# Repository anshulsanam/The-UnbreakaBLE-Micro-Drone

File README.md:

# The-UnbreakaBLE-Micro-Drone

This repo contains all the hardware for the drone including schematics, board files, and even 3d print files.

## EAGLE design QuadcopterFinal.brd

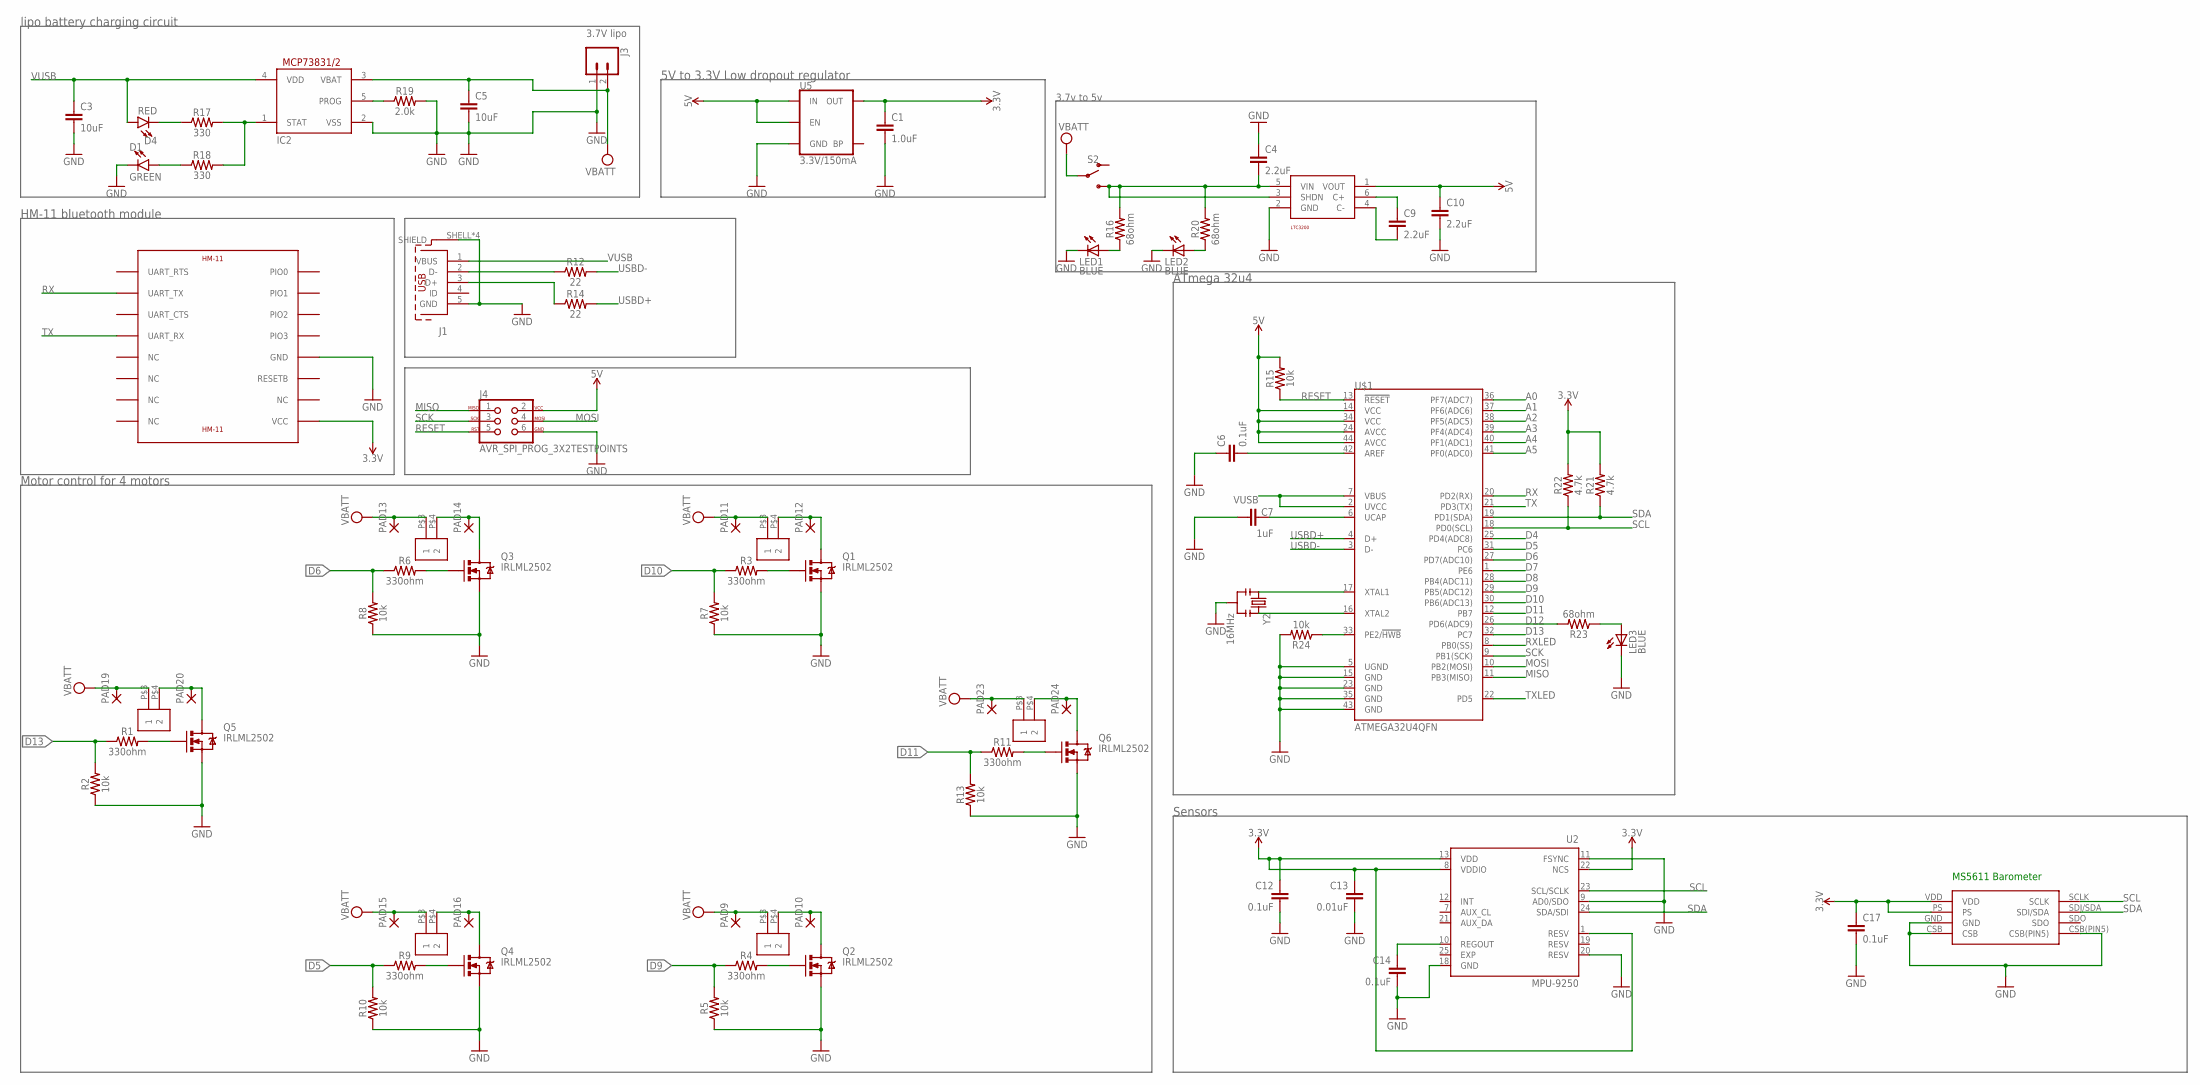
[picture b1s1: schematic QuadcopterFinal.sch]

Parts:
C1: 1.0uF; 0402
C3, C5: 10uF; 0603
C4, C9, C10: 2.2uF; 0603
C6, C12, C14, C17: 0.1uF; 0402
C7: 1uF; 0402
C13: 0.01uF; C0402
D1: GREEN; LED-0603
D4: RED; LED-0603
IC2: MCP73831/OT; SOT23-5L
J1: 629105136821
J3: CONN_021X02_NO_SILK; 1X02_NO_SILK
J4: AVR_SPI_PROG_3X2TESTPOINTS; 2X3_TEST_POINTS
LED1, LED2, LED3: BLUE; CHIPLED_1206
LTC3200: LTC3200
PAD9, PAD10, PAD11, PAD12, PAD13, PAD14, PAD15, PAD16, PAD19, PAD20, PAD23, PAD24: SMD2; SMD1,27-2,54
Q1, Q2, Q3, Q4, Q5, Q6: IRLML2502; SOT23
R1, R3, R4, R6, R9, R11: 330ohm; 0603
R2, R5, R7, R8, R10, R13, R15, R24: 10k; 0603
R12, R14: 22; 0402
R16, R20, R23: 68ohm; 0603
R17, R18: 330; 0603
R19: 2.0k; 0603
R21, R22: 4.7k; 0603
S2: SWITCH-SPDT-SMD-RIGHT-ANGLE; SWITCH_SPST_SMD_A
U2: MPU-9250; QFN40P300X300X105-25N
U5: 3.3V/150mA; SOT23-5
U$1: ATMEGA32U4QFN; SPARKFUN-DIGITALIC_QFN-44
U$2, U$3, U$4, U$5, U$7, U$8: QUADARM
U$6: HM-11
U$9: MS5611-01BA01
Y2: 16MHz; RESONATOR-SMD

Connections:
3.3V: C1.1, C12.1, C13.1, C17.1, R21.2, R22.2, U2.1 (RESV), U2.8 (VDDIO), U2.13 (VDD), U2.22 (NCS), U5.5 (OUT), U$6.VCC, U$9.PS, U$9.VDD
5V: C10.1, J4.2, LTC3200.1 (VOUT), R15.2, U5.1 (IN), U5.3 (EN), U$1.14 (VCC), U$1.24 (AVCC), U$1.34 (VCC), U$1.44 (AVCC)
A0: U$1.36 (PF7(ADC7))
A1: U$1.37 (PF6(ADC6))
A2: U$1.38 (PF5(ADC5))
A3: U$1.39 (PF4(ADC4))
A4: U$1.40 (PF1(ADC1))
A5: U$1.41 (PF0(ADC0))
D4: U$1.25 (PD4(ADC8))
D5: R9.1, R10.2, U$1.31 (PC6)
D6: R6.1, R8.2, U$1.27 (PD7(ADC10))
D7: U$1.1 (PE6)
D8: U$1.28 (PB4(ADC11))
D9: R4.1, R5.2, U$1.29 (PB5(ADC12))
D10: R3.1, R7.2, U$1.30 (PB6(ADC13))
D11: R11.1, R13.2, U$1.12 (PB7)
D12: R23.2, U$1.26 (PD6(ADC9))
D13: R1.1, R2.2, U$1.32 (PC7)
EXP: U2.25 (EXP)
GND: C1.2, C3.2, C4.1, C5.2, C6.1, C7.1, C10.2, C12.2, C13.2, C14.2, C17.2, D1.C, IC2.2 (VSS), J1.5 (GND), J1.SHELL (SHIELD), J1.SHELL1 (SHIELD), J1.SHELL2 (SHIELD), J1.SHELL3 (SHIELD), J3.1, J4.6, LED1.C, LED2.C, LED3.C, LTC3200.2 (GND), Q1.2 (S), Q2.2 (S), Q3.2 (S), Q4.2 (S), Q5.2 (S), Q6.2 (S), R2.1, R5.1, R7.1, R8.1, R10.1, R13.1, R19.2, R24.2, U2.9 (AD0/SDO), U2.11 (FSYNC), U2.18 (GND), U2.20 (RESV), U5.2 (GND), U$1.5 (UGND), U$1.15 (GND), U$1.23 (GND), U$1.35 (GND), U$1.43 (GND), U$6.GND, U$9.CSB, U$9.CSB(PIN5), U$9.GND, Y2.2
MISO: J4.1, U$1.11 (PB3(MISO))
MOSI: J4.4, U$1.10 (PB2(MOSI))
unnamed: Q5.1 (G), R1.2
unnamed: C4.2, LTC3200.3 (SHDN), LTC3200.5 (VIN), R16.2, R20.2, S2.3 (S)
unnamed: PAD20.1, Q5.3 (D), U$7.P$4 (2)
unnamed: Q6.1 (G), R11.2
unnamed: LED1.A, R16.1
unnamed: PAD24.1, Q6.3 (D), U$8.P$4 (2)
unnamed: Q1.1 (G), R3.2
unnamed: PAD12.1, Q1.3 (D), U$3.P$4 (2)
unnamed: LED2.A, R20.1
unnamed: Q2.1 (G), R4.2
unnamed: PAD10.1, Q2.3 (D), U$2.P$4 (2)
unnamed: J1.2 (D-), R12.1
unnamed: Q3.1 (G), R6.2
unnamed: PAD14.1, Q3.3 (D), U$4.P$4 (2)
unnamed: J1.3 (D+), R14.1
unnamed: Q4.1 (G), R9.2
unnamed: PAD16.1, Q4.3 (D), U$5.P$4 (2)
unnamed: U$1.17 (XTAL1), Y2.1
unnamed: C9.1, LTC3200.6 (C+)
unnamed: C14.1, U2.10 (REGOUT)
unnamed: C9.2, LTC3200.4 (C-)
unnamed: D4.C, R17.1
unnamed: IC2.1 (STAT), R17.2, R18.2
unnamed: D1.A, R18.1
unnamed: U$1.16 (XTAL2), Y2.3
unnamed: LED3.A, R23.1
unnamed: IC2.5 (PROG), R19.1
unnamed: R24.1, U$1.33 (PE2/!HWB)
unnamed: C6.2, U$1.42 (AREF)
unnamed: C7.2, U$1.6 (UCAP)
RESET: J4.5, R15.1, U$1.13 (!RESET)
RESV: U2.19 (RESV)
RX: U$1.20 (PD2(RX)), U$6.UART_TX
RXLED: U$1.8 (PB0(SS))
SCK: J4.3, U$1.9 (PB1(SCK))
SCL: R22.1, U2.23 (SCL/SCLK), U$1.18 (PD0(SCL)), U$9.SCLK
SDA: R21.1, U2.24 (SDA/SDI), U$1.19 (PD1(SDA)), U$9.SDI/SDA
TX: U$1.21 (PD3(TX)), U$6.UART_RX
TXLED: U$1.22 (PD5)
USBD+: R14.2, U$1.4 (D+)
USBD-: R12.2, U$1.3 (D-)
VDD: C5.1, IC2.3 (VBAT), J3.2, PAD9.1, PAD11.1, PAD13.1, PAD15.1, PAD19.1, PAD23.1, S2.2, U$2.P$3 (1), U$3.P$3 (1), U$4.P$3 (1), U$5.P$3 (1), U$7.P$3 (1), U$8.P$3 (1)
VUSB: C3.1, D4.A, IC2.4 (VDD), J1.1 (VBUS), U$1.2 (UVCC), U$1.7 (VBUS)

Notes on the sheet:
3.7V lipo
Sensors
5V to 3.3V Low dropout regulator
HM-11 bluetooth module
Motor control for 4 motors
ATmega 32u4
3.7v to 5v
MS5611 Barometer
lipo battery charging circuit

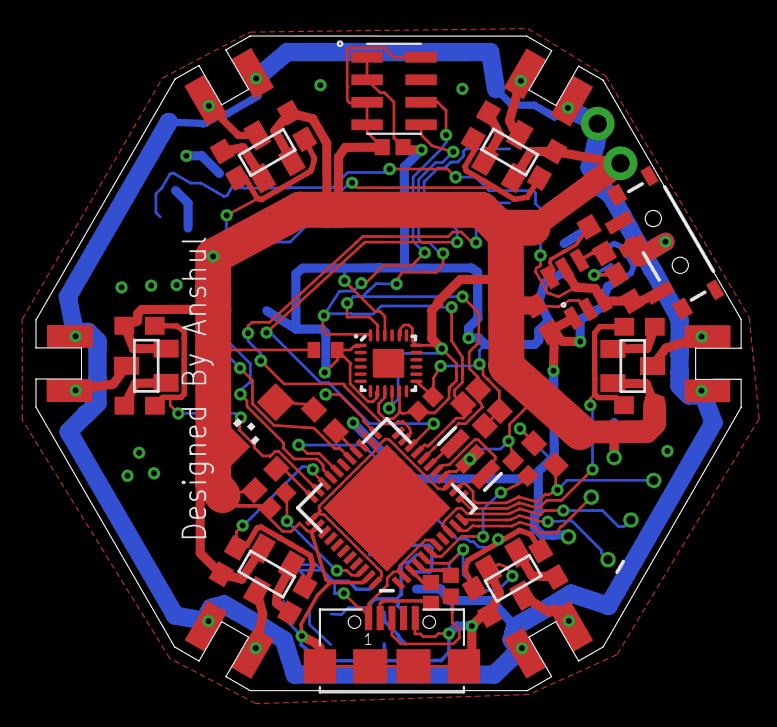
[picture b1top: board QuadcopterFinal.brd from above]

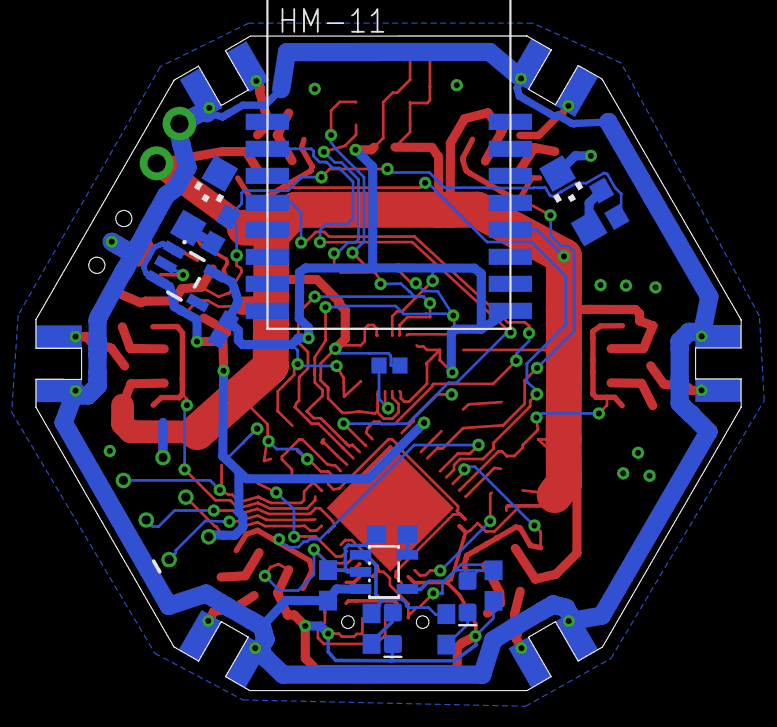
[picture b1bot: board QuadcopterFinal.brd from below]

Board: 2 copper layers, 39.2 x 36.4 mm, 77 parts (28 on the bottom side), 52 nets.

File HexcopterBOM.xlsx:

Qty | Value | Package | Parts |  | Link |  | Qty ordered | Unit Price
1 | PCBs |  |  |  | oshpark
1 |  | LTC3200 | LTC3200 |  | link |  | 2 | 0
1 | 0.01uF | 402 | C11 |  | link |  | 3 | 0.1
1 |  | SWITCH_SPST_SMD_A | S2 |  | link |  | 3 | 0.2
5 | 0.1UF | 402 | C6, C7, C12, C13, C17 |  | link |  | 15 | 0.03
1 | 0.22UF | 0603 | C14 |  | link |  | 3 | 0.1
1 | 1.0UF | 0402 | C1 |  | link |  | 3 | 0.1
1 | 2.0K | 0603 | R19 |  | link |  | 3 | 0.1
3 | 2.2UF | 0603 | C4, C9, C10 |  | link |  | 9 | 0.1
1 | 3.3V/150MA | SOT23-5 | U5 |  | link |  | 3 | 0.48
2 | 4.7K | 0603 | R21, R22 |  | link |  | 6 | 0.1
1 | 4.7UF | 0603 | C15 |  | link |  | 3 | 0.13
8 | 10K | 0603 | R2, R5, R7, R8, R10, R13, R15, R24 |  | link |  | 24 | 0.109
2 | 10UF | 0603 | C3, C5 |  | link |  | 6 | 0.15
1 | 16MHZ | RESONATOR-SMD | Y2 |  | link |  | 3 | 0.46
2 | 22 | 0402 | R12, R14 |  | link |  | 6 | 0.1
1 | 32U4 | QFN-44-NOPAD | U$1 |  |  |  | 3 | 0
8 | 330ohm | 0603 | R1, R3, R4, R6, R9, R11, R17, R18 |  | link |  | 24 | 2.5000000000000001E-2
3 | 68ohm | 603 | R16, R20, R23 |  | link |  | 9 | 0.1
3 | BLUE | CHIPLED_1206 | LED1, LED2, LED3 |  | link |  | 9 | 0
1 | GREEN | LED-0603 | D1 |  | link |  | 3 | 0.14000000000000001
1 | HM-11 | HM-11 | U$6 |  | link |  | 1 | 11.99
6 | IRLML2502 | SOT23 | Q1, Q2, Q3, Q4, Q5, Q6 |  | link |  | 12 | 0.31900000000000001
1 | MCP73831/OT | SOT23-5L | IC2 |  | link |  | 3 | 0.6
1 | MPU-9250 | QFN-24-EP | U3 |  | link |  | 1 | 8.66
1 | MS5611-01BA01 | MS5611-01BA01 | U$9 |  | link |  | 1 | 13.242000000000001
1 | RED | LED-0603 | D4 |  | link |  | 3 | 0.14000000000000001
1 | USB-MICROB | USB-MICROB | J1 |  | link |  | 3 | 1.21
 | battery |  |  |  | link
 |  |  |  |  |  |  | total = | 56.56600000000001

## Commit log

2017-07-24 Open Source Files for UnbreaBLE drone project

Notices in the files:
parts and their libraries:
SparkFun-FreqCtrl: Licensing: CC v3.0 Share-Alike You are welcome to use this library for commercial purposes.
SparkFun-Resistors: Licensing: Creative Commons ShareAlike 4.0 International - https://creativecommons.org/licenses/by-sa/4.0
